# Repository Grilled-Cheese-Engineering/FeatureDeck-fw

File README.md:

# FeatureDeck

This is a board designed to assist with programming showfiles in GrandMA3 by allowing the user to fine tune encoder values. The board comes with 5 rotary encoders and 3 extra buttons (with hot swap sockets). The board outputs MIDI to the host computer which also allows for compatibility with software other than GrandMA3.

More details coming soon...

# Pictures

Coming soon...

# Build Guide

Coming soon...

# Credits

- PCB Design by Josh Carlson (JStudios6118)

- Firmware by Lucas Moidel

- MA3 Plugin (coming soon) by Josh Carlson (JStudios6118)

---

### Disclaimer

This project is not associated or officially recognized by the MA Lighting company or the GrandMA3 product line in any way. This is just a project for a DIY control surface that works with the software.

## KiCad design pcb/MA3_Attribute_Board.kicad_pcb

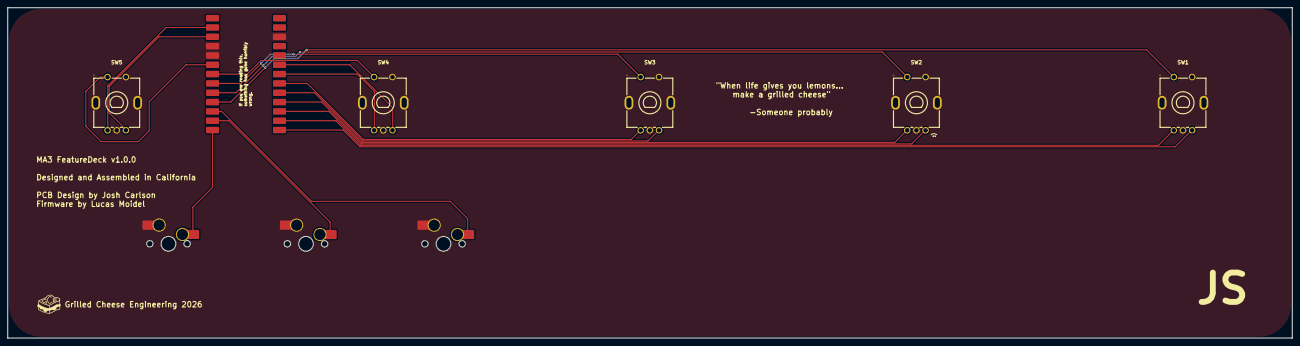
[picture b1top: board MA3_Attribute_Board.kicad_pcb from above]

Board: 2 copper layers, 350.0 x 90.0 mm, 9 parts (0 on the bottom side), 19 nets.

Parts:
S1, S2, S3: MX_Hotswap_1.75u
SW1, SW2, SW3, SW4, SW5: RotaryEncoder; SW-TH_PEC11R-4XXXF-SXXXX
U1: Adafruit_KB2040_SMD

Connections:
/Button 1: S1.1, U1.13 (9/PB5)
/Button 2: S2.1, U1.12 (8/PB4)
/Button 3: S3.1, U1.11 (7/PE6)
/Encoder 1A: SW1.A, U1.25 (16/PB2)
/Encoder 1B: SW1.B, U1.26 (10/PB6)
/Encoder 2A: SW2.A, U1.23 (15/PB1)
/Encoder 2B: SW2.B, U1.24 (14/PB3)
/Encoder 3A: SW3.A, U1.21 (A1/PF6)
/Encoder 3B: SW3.B, U1.22 (A0/PF7)
/Encoder 4A: SW4.A, U1.20 (A2/PF5)
/Encoder 4B: SW4.B, U1.19 (A3/PF4)
/Encoder 5A: SW5.A, U1.2 (TX0/PD3)
/Encoder 5B: SW5.B, U1.3 (RX1/PD2)
/Enoder Mode 1: SW1.S1, U1.10 (6/PD7)
/Enoder Mode 2: SW2.S1, U1.9 (5/PC6)
/Enoder Mode 3: SW3.S1, U1.8 (4/PD4)
/Enoder Mode 4: SW4.S1, U1.7 (3/PD0)
/Enoder Mode 5: SW5.S1, U1.6 (2/PD1)
GND: S1.2, S2.2, S3.2, SW1.C, SW1.MP, SW1.S2, SW2.C, SW2.MP, SW2.S2, SW3.C, SW3.MP, SW3.S2, SW4.C, SW4.MP, SW4.S2, SW5.C, SW5.MP, SW5.S2, U1.4 (GND), U1.5 (GND), U1.16 (GND)

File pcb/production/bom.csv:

Designator,Footprint,Quantity,Value,LCSC Part #
"S1, S2, S3",MX_Hotswap_1.75u,3,~,
"SW1, SW2, SW3, SW4, SW5",SW-TH_PEC11R-4XXXF-SXXXX,5,RotaryEncoder,
U1,Adafruit_KB2040_SMD,1,~,
